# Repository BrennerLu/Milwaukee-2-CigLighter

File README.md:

# MilwaukeeM18-2-CarCigaretteLighter

There will be a redesign in the near future using the findings of [Tool Scientist](https://www.youtube.com/watch?v=q7spzrIbdKY). By using the official M18 battery protocol, the design will be more reliable while reducing cost and complexity.

## Description

A small device compatible with the Milwaukee M18 range of batteries. It contains an undervoltage lockout as well as a buck converter that delivers 14 volts at 15 amps to a cigarette lighter socket found in most cars. It can be used to power car-ready devices such as USB-PD chargers, camping fridges and inverters.

## Features

- Outputs clean 14V / 15A DC
- Snaps directly into Milwaukee M18 batteries
- Maximum current reduction for small battery sizes such as 2.0Ah
- Two stage over current protection
  - Smooth overcurrent protection by reducing the duty cycle of the buck converter
  - Short-circuit protection via LP mini-blade fuse (commonly found in modern vehicles)
- Undervoltage lockout at 15.5V

## Thanks to
- [oxullo](https://github.com/oxullo) for providing the CAM jobs, design rules and ulps used in this project

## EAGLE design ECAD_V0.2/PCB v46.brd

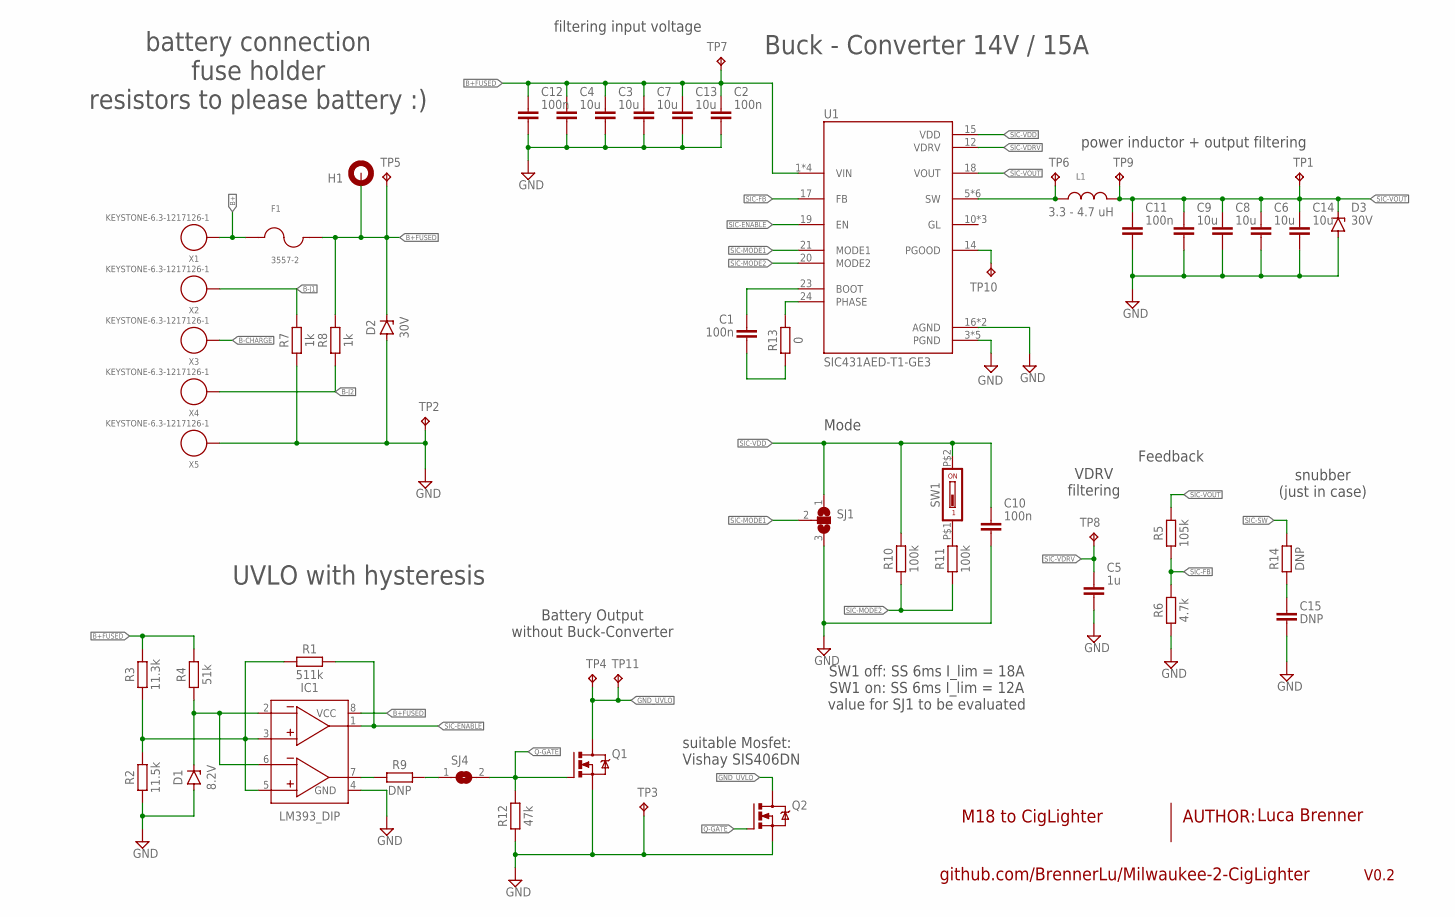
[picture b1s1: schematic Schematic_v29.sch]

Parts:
C1, C2, C10, C11, C12: 100n; CAPC1608X85
C3, C4, C6, C7, C8, C9, C13, C14: 10u; CAPC3225X135
C5: 1u; CAPC3216X135
C15: DNP; CAPC1608X85
D1: 8.2V; DIOMELF3516
D2, D3: 30V; DIOM5336X265N
F1: 3557-2; FUSE_3557-2
H1: MOUNT-PAD-ROUND2.8; 2,8-PAD
IC1: LM393_DIP; DIP826W53P254L959H508Q8B
L1: 3.3 - 4.7 uH; AMDLA1707S-3R3MT-FP
Q1, Q2: VISHAY-SIS406DN; POWERPAK-1212-8-SINGLE
R1: 511k; RESC2012X65
R2: 11.5k; RESC2012X65
R3: 11.3k; RESC2012X65
R4: 51k; RESC2012X65
R5: 105k; RESC2012X65
R6: 4.7k; RESC2012X65
R7, R8: 1k; RESC2012X65
R9: DNP; RESC2012X65
R10, R11: 100k; RESC2012X65
R12: 47k; RESC2012X65
R13: 0; RESC1608X60
R14: DNP; RESC1608X60
SJ1: SJ2WW; SJ_2W
SJ4: SJ
SW1: DS04-254-SMT; DIPSW-SMD-254
TP1, TP2, TP3, TP4, TP5, TP11: TPPAD1-20; P1-20
TP6, TP7, TP8, TP9: TPB1,27; B1,27
TP10: TPTP06R; TP06R
U1: SIC431AED-T1-GE3; REGULATOR_SIC431AED-T1-GE3
X1, X2, X3, X4, X5: KEYSTONE-6.3-1217126-1; KEYSTONE.6.3-1217126-1-FP

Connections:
B+: F1.1_1 (1), F1.1_2 (1), X1.P$1, X1.P$2
B+FUSED: C2.1, C3.1, C4.1, C7.1, C12.1, C13.1, D2.1 (C), F1.2_1 (2), F1.2_2 (2), H1.B2,8, IC1.8 (VCC), R3.2, R4.2, R8.1, TP5.TP, TP7.TP, U1.1 (VIN), U1.2 (VIN), U1.22 (VIN), U1.26 (VIN)
B-CHARGE: X3.P$1, X3.P$2
B-J1: R7.1, X2.P$1, X2.P$2
B-J2: R8.2, X4.P$1, X4.P$2
GND: C2.2, C3.2, C4.2, C5.2, C6.2, C7.2, C8.2, C9.2, C10.2, C11.2, C12.2, C13.2, C14.2, C15.1, D1.2 (A), D2.2 (A), D3.2 (A), IC1.4 (GND), Q1.S1 (S), Q1.S2 (S), Q1.S3 (S), Q2.S1 (S), Q2.S2 (S), Q2.S3 (S), R2.1, R6.1, R7.2, R12.1, SJ1.3, TP2.TP, TP3.TP, U1.3 (PGND), U1.4 (PGND), U1.13 (PGND), U1.16 (AGND), U1.25 (AGND), U1.27_1 (PGND), U1.27_2 (PGND), X5.P$1, X5.P$2
GND_UVLO: Q1.D1 (D), Q1.D2 (D), Q1.D3 (D), Q1.D4 (D), Q1.D-PAD (D), Q2.D1 (D), Q2.D2 (D), Q2.D3 (D), Q2.D4 (D), Q2.D-PAD (D), TP4.TP, TP11.TP
unnamed: R11.2, SW1.P$1 (1)
unnamed: D1.1 (C), IC1.2 (-IN1), IC1.6 (-IN2), R4.1
unnamed: IC1.3 (+IN1), IC1.5 (+IN2), R1.1, R2.2, R3.1
unnamed: IC1.7 (OUT2), R9.1
unnamed: R9.2, SJ4.1
unnamed: TP10.TP, U1.14 (PGOOD)
unnamed: R13.2, U1.24 (PHASE)
unnamed: C15.2, R14.1
Q-GATE: Q1.G, Q2.G, R12.2, SJ4.2
SIC-BOOT: C1.2, U1.23 (BOOT)
SIC-ENABLE: IC1.1 (OUT1), R1.2, U1.19 (EN)
SIC-FB: R5.1, R6.2, U1.17 (FB)
SIC-MODE1: SJ1.2, U1.21 (MODE1)
SIC-MODE2: R10.1, R11.1, U1.20 (MODE2)
SIC-PHASE: C1.1, R13.1
SIC-SW: L1.P$1 (1), R14.2, TP6.TP, U1.5 (SW), U1.6 (SW), U1.7 (SW), U1.8 (SW), U1.9 (SW), U1.9.1 (SW)
SIC-VDD: C10.1, R10.2, SJ1.1, SW1.P$2 (2), U1.15 (VDD)
SIC-VDRV: C5.1, TP8.TP, U1.12 (VDRV)
SIC-VOUT: C6.1, C8.1, C9.1, C11.1, C14.1, D3.1 (C), L1.P$2 (2), R5.2, TP1.TP, TP9.TP, U1.18 (VOUT)

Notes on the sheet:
filtering input voltage
Feedback
Mode
VDRV filtering
battery connection fuse holder resistors to please battery :)
AUTHOR:
UVLO with hysteresis
Battery Output without Buck-Converter
power inductor + output filtering
Buck - Converter 14V / 15A
SW1 off: SS 6ms I_lim = 18A SW1 on: SS 6ms I_lim = 12A value for SJ1 to be evaluated
V0.2
M18 to CigLighter
snubber (just in case)
suitable Mosfet: Vishay SIS406DN

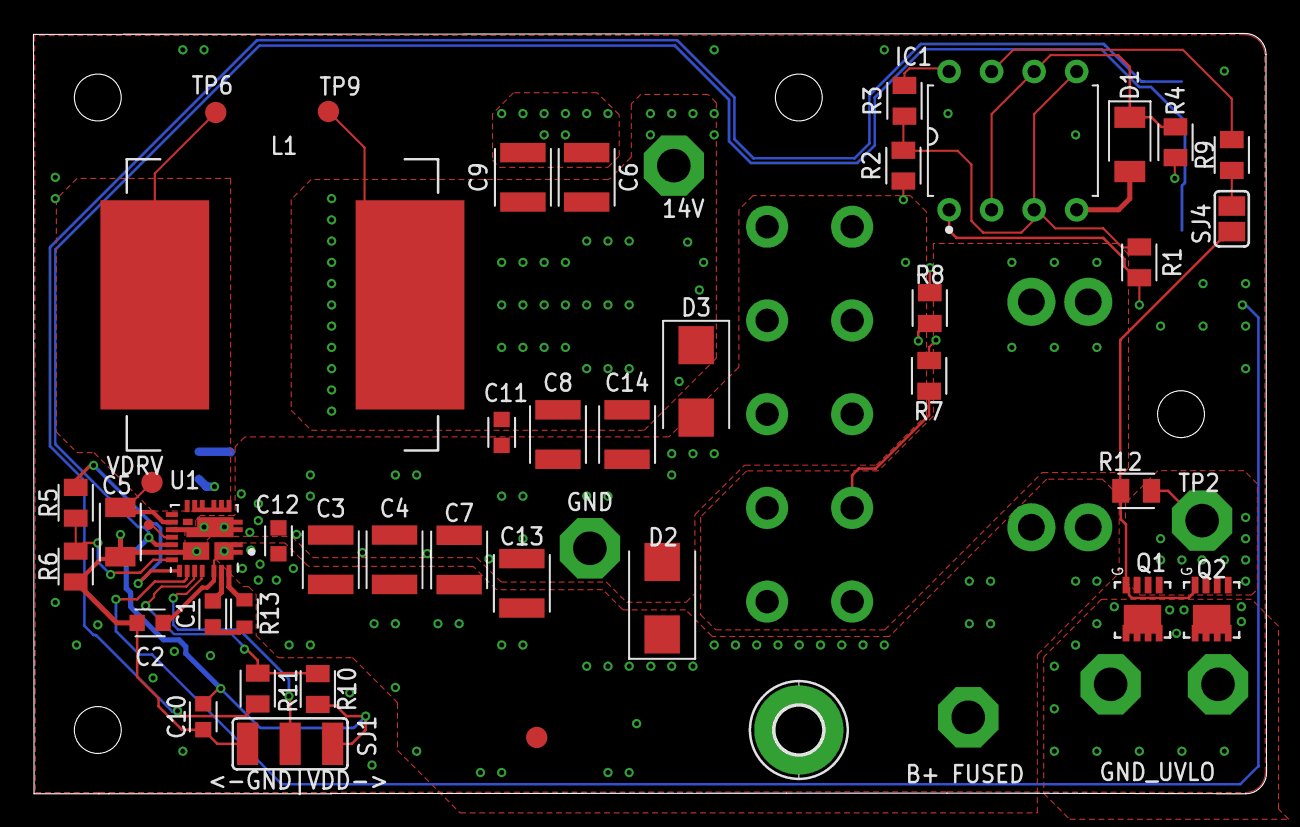
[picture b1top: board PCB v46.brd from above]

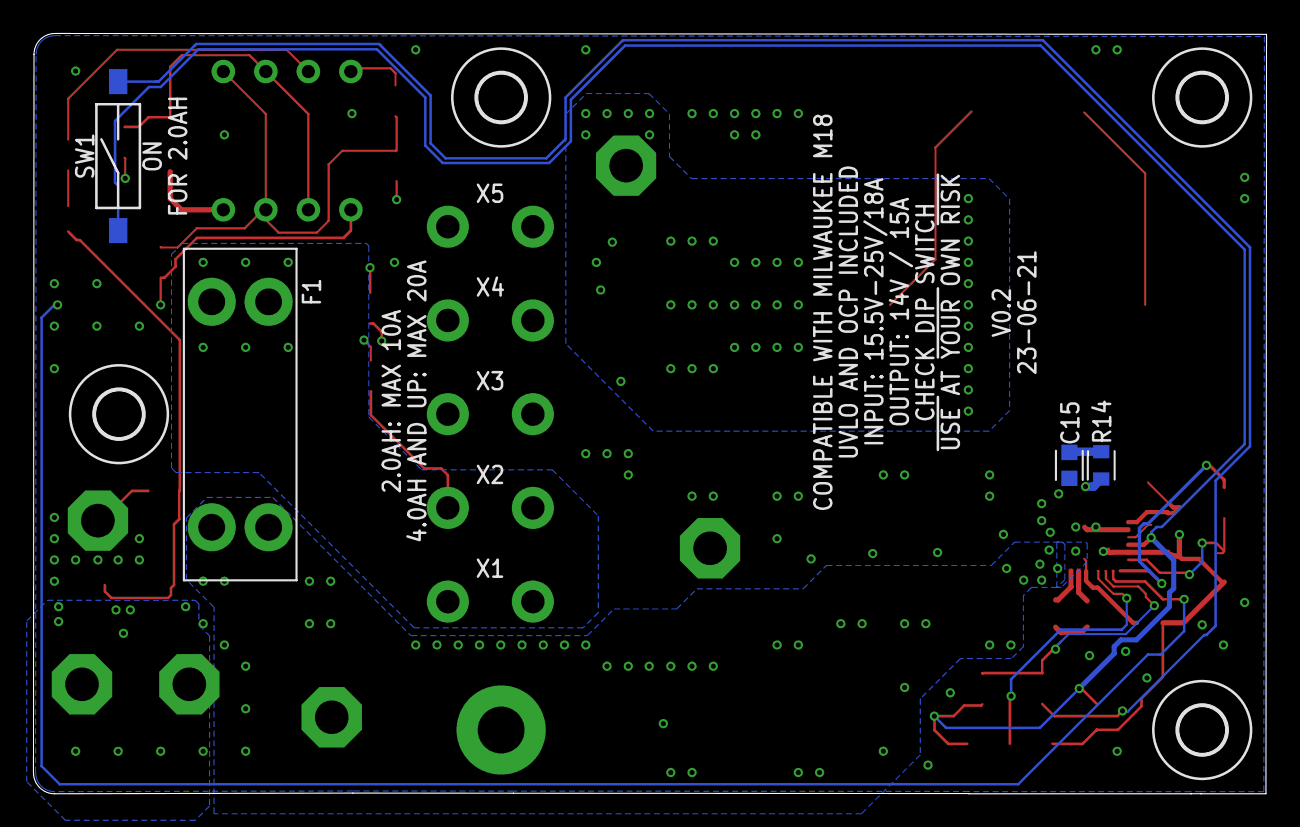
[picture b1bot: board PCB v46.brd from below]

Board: 4 copper layers, 73.7 x 45.4 mm, 62 parts (13 on the bottom side), 26 nets.

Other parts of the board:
U$1, U$4, U$5, U$6: 2,8

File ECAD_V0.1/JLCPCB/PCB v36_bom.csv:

Comment,Designator,Footprint,LCSC Part #
,R9,RESC2012X65,
,SJ4,SJ,
,SJ1,SJ_2W,
1k,R7 R8,RESC2012X65,
1u,C5,CAPC3216X135,
3.3 - 4.7 uH,L1,AMDLA1707S-3R3MT-FP,
4.7k,R6,RESC2012X65,
8.2V,D1,DIOMELF3516,
10u,C3 C4 C6 C7 C8 C9 C13 C14,CAPC3225X135,
11.3k,R3,RESC2012X65,
11.5k,R2,RESC2012X65,
47k,R12,RESC2012X65,
51k,R4,RESC2012X65,
100n,C1 C2 C10 C11 C12,CAPC1608X85,
105k,R5,RESC2012X65,
200k,R10 R11,RESC2012X65,
511k,R1,RESC2012X65,
3557-2,F1,FUSE_3557-2,
DMN1004UFV,Q1,POWERDI3333-8-UX,
DS04-254-SMT,SW1,DIPSW-SMD-254,
KEYSTONE-6.3-1217126-1,X1 X2 X3 X4 X5,KEYSTONE.6.3-1217126-1-FP,
LM393_DIP,IC1,DIP826W53P254L959H508Q8B,
MOUNT-PAD-ROUND2.8,H1,2 8-PAD,
SIC431AED-T1-GE3,U1,REGULATOR_SIC431AED-T1-GE3,
TPB1 27,TP6 TP7 TP8 TP9,B1 27,
TPPAD1-20,TP1 TP2 TP3 TP4 TP5,P1-20,
TPTP06R,TP10,TP06R,

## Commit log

2023-05-18 Added files for production
2023-05-18 added schematic for first production pcb
2023-05-18 restructered folders
2023-05-19 Added Fusion Archive Files
2023-05-20 added new images
2023-05-20 modified readme.md
2023-06-21 New optional mosfets, Thermal Vias under SIC431, minor layout changes
2023-07-12 created schematic pdf
2024-02-26 new links to renders
2024-02-26 renamed pictures
2024-02-26 changed readme
